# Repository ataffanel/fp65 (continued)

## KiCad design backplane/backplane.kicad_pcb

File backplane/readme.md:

# 4 Board FP65 backplane

Backplane that can accept 4 FP65 boards and that can be chained to other backplane to accomodate bigger system.

A power supply can optionaly be soldered in order to provide up to 5V 1A to the system.
One of the board can also provide power for the system.

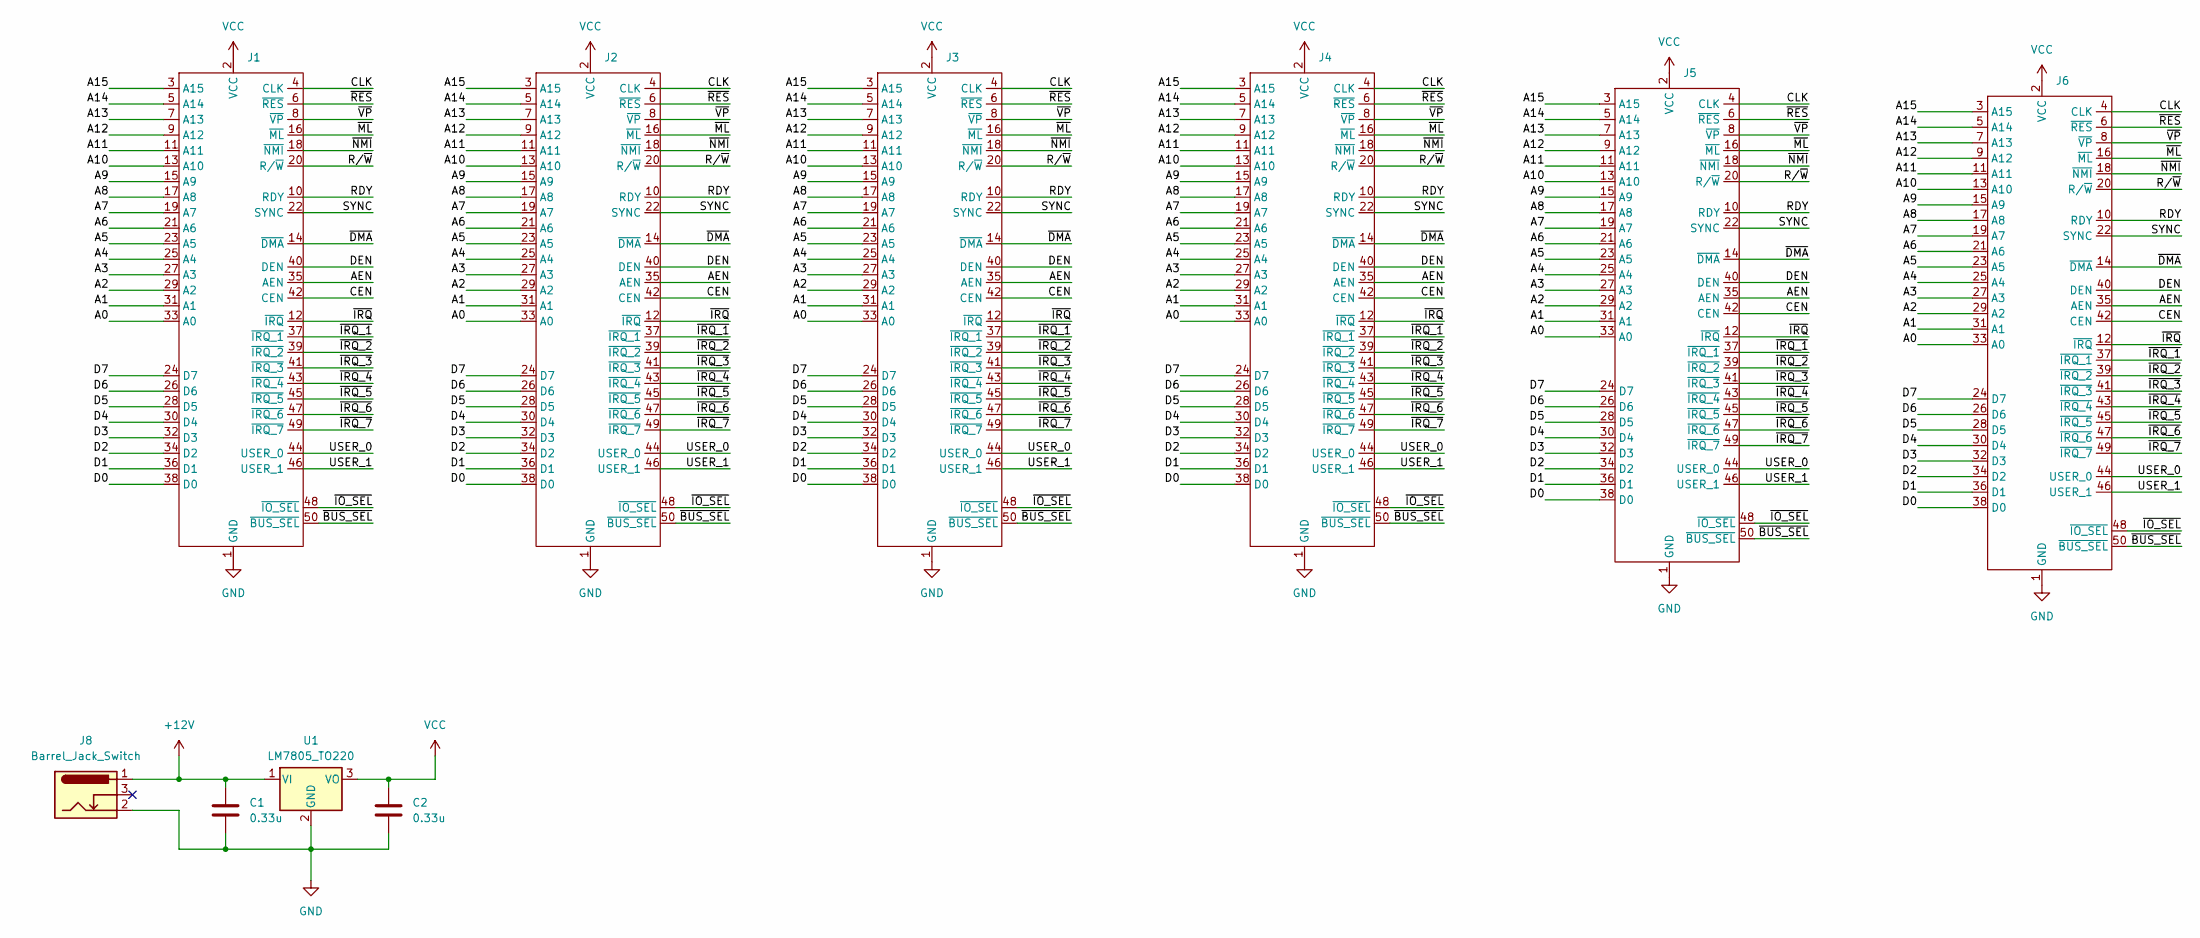
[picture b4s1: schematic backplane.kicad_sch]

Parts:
C1, C2: 0.33u; C_Disc_D5.0mm_W2.5mm_P5.00mm
J1: PinSocket_2x25_P2.54mm_Horizontal
J2, J3, J4, J5: PinSocket_2x25_P2.54mm_Vertical
J6: PinHeader_2x25_P2.54mm_Horizontal
J8: Barrel_Jack_Switch; BarrelJack_GCT_DCJ200-10-A_Horizontal
U1: LM7805_TO220; TO-220-3_Vertical

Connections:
+12V: C1.1, J8.1, U1.1 (VI)
/A0: J1.33 (A0), J2.33 (A0), J3.33 (A0), J4.33 (A0), J5.33 (A0), J6.33 (A0)
/A1: J1.31 (A1), J2.31 (A1), J3.31 (A1), J4.31 (A1), J5.31 (A1), J6.31 (A1)
/A2: J1.29 (A2), J2.29 (A2), J3.29 (A2), J4.29 (A2), J5.29 (A2), J6.29 (A2)
/A3: J1.27 (A3), J2.27 (A3), J3.27 (A3), J4.27 (A3), J5.27 (A3), J6.27 (A3)
/A4: J1.25 (A4), J2.25 (A4), J3.25 (A4), J4.25 (A4), J5.25 (A4), J6.25 (A4)
/A5: J1.23 (A5), J2.23 (A5), J3.23 (A5), J4.23 (A5), J5.23 (A5), J6.23 (A5)
/A6: J1.21 (A6), J2.21 (A6), J3.21 (A6), J4.21 (A6), J5.21 (A6), J6.21 (A6)
/A7: J1.19 (A7), J2.19 (A7), J3.19 (A7), J4.19 (A7), J5.19 (A7), J6.19 (A7)
/A8: J1.17 (A8), J2.17 (A8), J3.17 (A8), J4.17 (A8), J5.17 (A8), J6.17 (A8)
/A9: J1.15 (A9), J2.15 (A9), J3.15 (A9), J4.15 (A9), J5.15 (A9), J6.15 (A9)
/A10: J1.13 (A10), J2.13 (A10), J3.13 (A10), J4.13 (A10), J5.13 (A10), J6.13 (A10)
/A11: J1.11 (A11), J2.11 (A11), J3.11 (A11), J4.11 (A11), J5.11 (A11), J6.11 (A11)
/A12: J1.9 (A12), J2.9 (A12), J3.9 (A12), J4.9 (A12), J5.9 (A12), J6.9 (A12)
/A13: J1.7 (A13), J2.7 (A13), J3.7 (A13), J4.7 (A13), J5.7 (A13), J6.7 (A13)
/A14: J1.5 (A14), J2.5 (A14), J3.5 (A14), J4.5 (A14), J5.5 (A14), J6.5 (A14)
/A15: J1.3 (A15), J2.3 (A15), J3.3 (A15), J4.3 (A15), J5.3 (A15), J6.3 (A15)
/AEN: J1.35 (AEN), J2.35 (AEN), J3.35 (AEN), J4.35 (AEN), J5.35 (AEN), J6.35 (AEN)
/CEN: J1.42 (CEN), J2.42 (CEN), J3.42 (CEN), J4.42 (CEN), J5.42 (CEN), J6.42 (CEN)
/CLK: J1.4 (CLK), J2.4 (CLK), J3.4 (CLK), J4.4 (CLK), J5.4 (CLK), J6.4 (CLK)
/D0: J1.38 (D0), J2.38 (D0), J3.38 (D0), J4.38 (D0), J5.38 (D0), J6.38 (D0)
/D1: J1.36 (D1), J2.36 (D1), J3.36 (D1), J4.36 (D1), J5.36 (D1), J6.36 (D1)
/D2: J1.34 (D2), J2.34 (D2), J3.34 (D2), J4.34 (D2), J5.34 (D2), J6.34 (D2)
/D3: J1.32 (D3), J2.32 (D3), J3.32 (D3), J4.32 (D3), J5.32 (D3), J6.32 (D3)
/D4: J1.30 (D4), J2.30 (D4), J3.30 (D4), J4.30 (D4), J5.30 (D4), J6.30 (D4)
/D5: J1.28 (D5), J2.28 (D5), J3.28 (D5), J4.28 (D5), J5.28 (D5), J6.28 (D5)
/D6: J1.26 (D6), J2.26 (D6), J3.26 (D6), J4.26 (D6), J5.26 (D6), J6.26 (D6)
/D7: J1.24 (D7), J2.24 (D7), J3.24 (D7), J4.24 (D7), J5.24 (D7), J6.24 (D7)
/DEN: J1.40 (DEN), J2.40 (DEN), J3.40 (DEN), J4.40 (DEN), J5.40 (DEN), J6.40 (DEN)
/RDY: J1.10 (RDY), J2.10 (RDY), J3.10 (RDY), J4.10 (RDY), J5.10 (RDY), J6.10 (RDY)
/R/~W: J1.20 (R/~W), J2.20 (R/~W), J3.20 (R/~W), J4.20 (R/~W), J5.20 (R/~W), J6.20 (R/~W)
/SYNC: J1.22 (SYNC), J2.22 (SYNC), J3.22 (SYNC), J4.22 (SYNC), J5.22 (SYNC), J6.22 (SYNC)
/USER_0: J1.44 (USER_0), J2.44 (USER_0), J3.44 (USER_0), J4.44 (USER_0), J5.44 (USER_0), J6.44 (USER_0)
/USER_1: J1.46 (USER_1), J2.46 (USER_1), J3.46 (USER_1), J4.46 (USER_1), J5.46 (USER_1), J6.46 (USER_1)
/~BUS_SEL: J1.50 (~BUS_SEL), J2.50 (~BUS_SEL), J3.50 (~BUS_SEL), J4.50 (~BUS_SEL), J5.50 (~BUS_SEL), J6.50 (~BUS_SEL)
/~DMA: J1.14 (~DMA), J2.14 (~DMA), J3.14 (~DMA), J4.14 (~DMA), J5.14 (~DMA), J6.14 (~DMA)
/~IO_SEL: J1.48 (~IO_SEL), J2.48 (~IO_SEL), J3.48 (~IO_SEL), J4.48 (~IO_SEL), J5.48 (~IO_SEL), J6.48 (~IO_SEL)
/~IRQ_1: J1.37 (~IRQ_1), J2.37 (~IRQ_1), J3.37 (~IRQ_1), J4.37 (~IRQ_1), J5.37 (~IRQ_1), J6.37 (~IRQ_1)
/~IRQ_2: J1.39 (~IRQ_2), J2.39 (~IRQ_2), J3.39 (~IRQ_2), J4.39 (~IRQ_2), J5.39 (~IRQ_2), J6.39 (~IRQ_2)
/~IRQ_3: J1.41 (~IRQ_3), J2.41 (~IRQ_3), J3.41 (~IRQ_3), J4.41 (~IRQ_3), J5.41 (~IRQ_3), J6.41 (~IRQ_3)
/~IRQ_4: J1.43 (~IRQ_4), J2.43 (~IRQ_4), J3.43 (~IRQ_4), J4.43 (~IRQ_4), J5.43 (~IRQ_4), J6.43 (~IRQ_4)
/~IRQ_5: J1.45 (~IRQ_5), J2.45 (~IRQ_5), J3.45 (~IRQ_5), J4.45 (~IRQ_5), J5.45 (~IRQ_5), J6.45 (~IRQ_5)
/~IRQ_6: J1.47 (~IRQ_6), J2.47 (~IRQ_6), J3.47 (~IRQ_6), J4.47 (~IRQ_6), J5.47 (~IRQ_6), J6.47 (~IRQ_6)
/~IRQ_7: J1.49 (~IRQ_7), J2.49 (~IRQ_7), J3.49 (~IRQ_7), J4.49 (~IRQ_7), J5.49 (~IRQ_7), J6.49 (~IRQ_7)
/~IRQ: J1.12 (~IRQ), J2.12 (~IRQ), J3.12 (~IRQ), J4.12 (~IRQ), J5.12 (~IRQ), J6.12 (~IRQ)
/~ML: J1.16 (~ML), J2.16 (~ML), J3.16 (~ML), J4.16 (~ML), J5.16 (~ML), J6.16 (~ML)
/~NMI: J1.18 (~NMI), J2.18 (~NMI), J3.18 (~NMI), J4.18 (~NMI), J5.18 (~NMI), J6.18 (~NMI)
/~RES: J1.6 (~RES), J2.6 (~RES), J3.6 (~RES), J4.6 (~RES), J5.6 (~RES), J6.6 (~RES)
/~VP: J1.8 (~VP), J2.8 (~VP), J3.8 (~VP), J4.8 (~VP), J5.8 (~VP), J6.8 (~VP)
GND: C1.2, C2.2, J1.1 (GND), J2.1 (GND), J3.1 (GND), J4.1 (GND), J5.1 (GND), J6.1 (GND), J8.2, U1.2 (GND)
VCC: C2.1, J1.2 (VCC), J2.2 (VCC), J3.2 (VCC), J4.2 (VCC), J5.2 (VCC), J6.2 (VCC), U1.3 (VO)

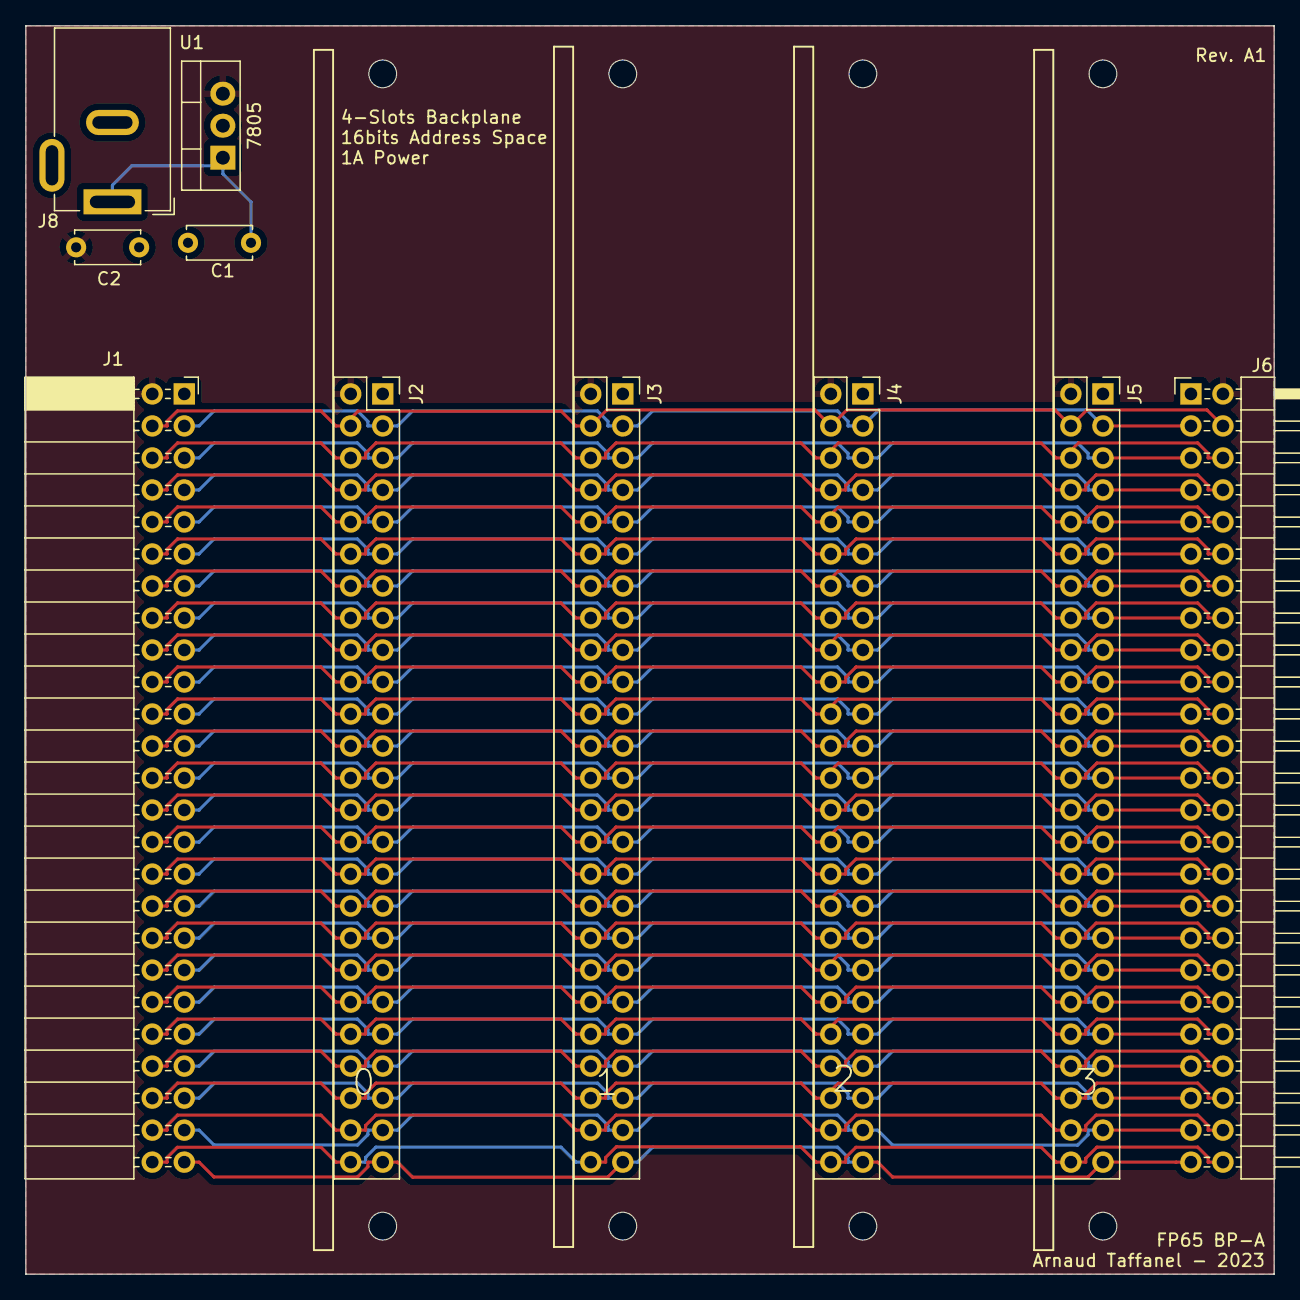
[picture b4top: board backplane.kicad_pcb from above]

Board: 2 copper layers, 99.1 x 99.1 mm, 10 parts (0 on the bottom side), 51 nets.

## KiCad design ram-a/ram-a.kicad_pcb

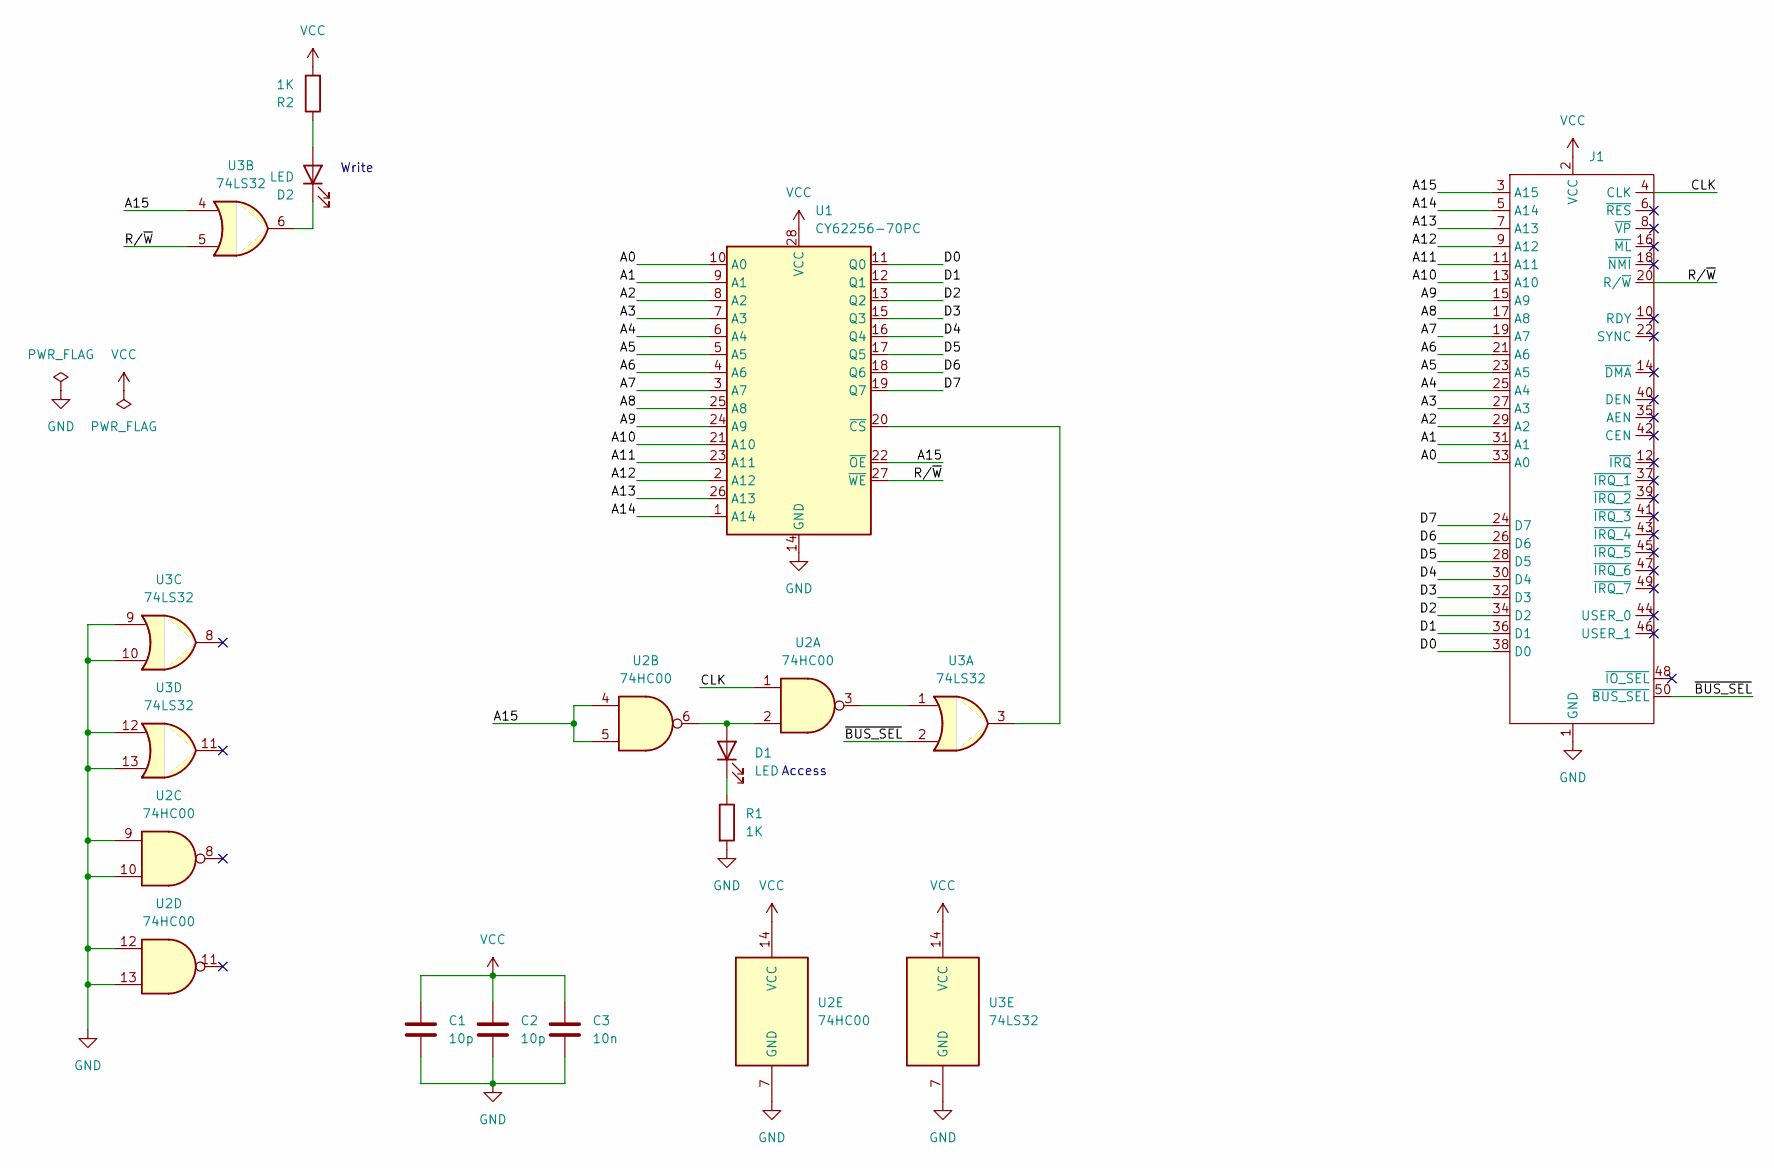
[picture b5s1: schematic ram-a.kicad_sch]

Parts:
C1, C2: 10p; C_Disc_D4.3mm_W1.9mm_P5.00mm
C3: 10n; C_Disc_D4.3mm_W1.9mm_P5.00mm
D1, D2: LED; LED_D3.0mm_Horizontal_O1.27mm_Z2.0mm
J1: PinHeader_2x25_P2.54mm_Horizontal
R1, R2: 1K; R_Axial_DIN0204_L3.6mm_D1.6mm_P7.62mm_Horizontal
U1: CY62256-70PC; DIP-28_W15.24mm
U2: 74HC00; DIP-14_W7.62mm
U3: 74LS32; DIP-14_W7.62mm

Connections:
/A0: J1.33 (A0), U1.10 (A0)
/A1: J1.31 (A1), U1.9 (A1)
/A2: J1.29 (A2), U1.8 (A2)
/A3: J1.27 (A3), U1.7 (A3)
/A4: J1.25 (A4), U1.6 (A4)
/A5: J1.23 (A5), U1.5 (A5)
/A6: J1.21 (A6), U1.4 (A6)
/A7: J1.19 (A7), U1.3 (A7)
/A8: J1.17 (A8), U1.25 (A8)
/A9: J1.15 (A9), U1.24 (A9)
/A10: J1.13 (A10), U1.21 (A10)
/A11: J1.11 (A11), U1.23 (A11)
/A12: J1.9 (A12), U1.2 (A12)
/A13: J1.7 (A13), U1.26 (A13)
/A14: J1.5 (A14), U1.1 (A14)
/A15: J1.3 (A15), U1.22 (~OE), U2.4, U2.5, U3.4
/CLK: J1.4 (CLK), U2.1
/D0: J1.38 (D0), U1.11 (Q0)
/D1: J1.36 (D1), U1.12 (Q1)
/D2: J1.34 (D2), U1.13 (Q2)
/D3: J1.32 (D3), U1.15 (Q3)
/D4: J1.30 (D4), U1.16 (Q4)
/D5: J1.28 (D5), U1.17 (Q5)
/D6: J1.26 (D6), U1.18 (Q6)
/D7: J1.24 (D7), U1.19 (Q7)
/R/~W: J1.20 (R/~W), U1.27 (~WE), U3.5
/~BUS_SEL: J1.50 (~BUS_SEL), U3.2
GND: C1.2, C2.2, C3.2, J1.1 (GND), R1.2, U1.14 (GND), U2.7 (GND), U2.9, U2.10, U2.12, U2.13, U3.7 (GND), U3.9, U3.10, U3.12, U3.13
unnamed: D1.2 (A), U2.2, U2.6
unnamed: D1.1 (K), R1.1
unnamed: D2.2 (A), R2.1
unnamed: D2.1 (K), U3.6
unnamed: U1.20 (~CS), U3.3
unnamed: U2.3, U3.1
VCC: C1.1, C2.1, C3.1, J1.2 (VCC), R2.2, U1.28 (VCC), U2.14 (VCC), U3.14 (VCC)

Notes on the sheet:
Access
Write

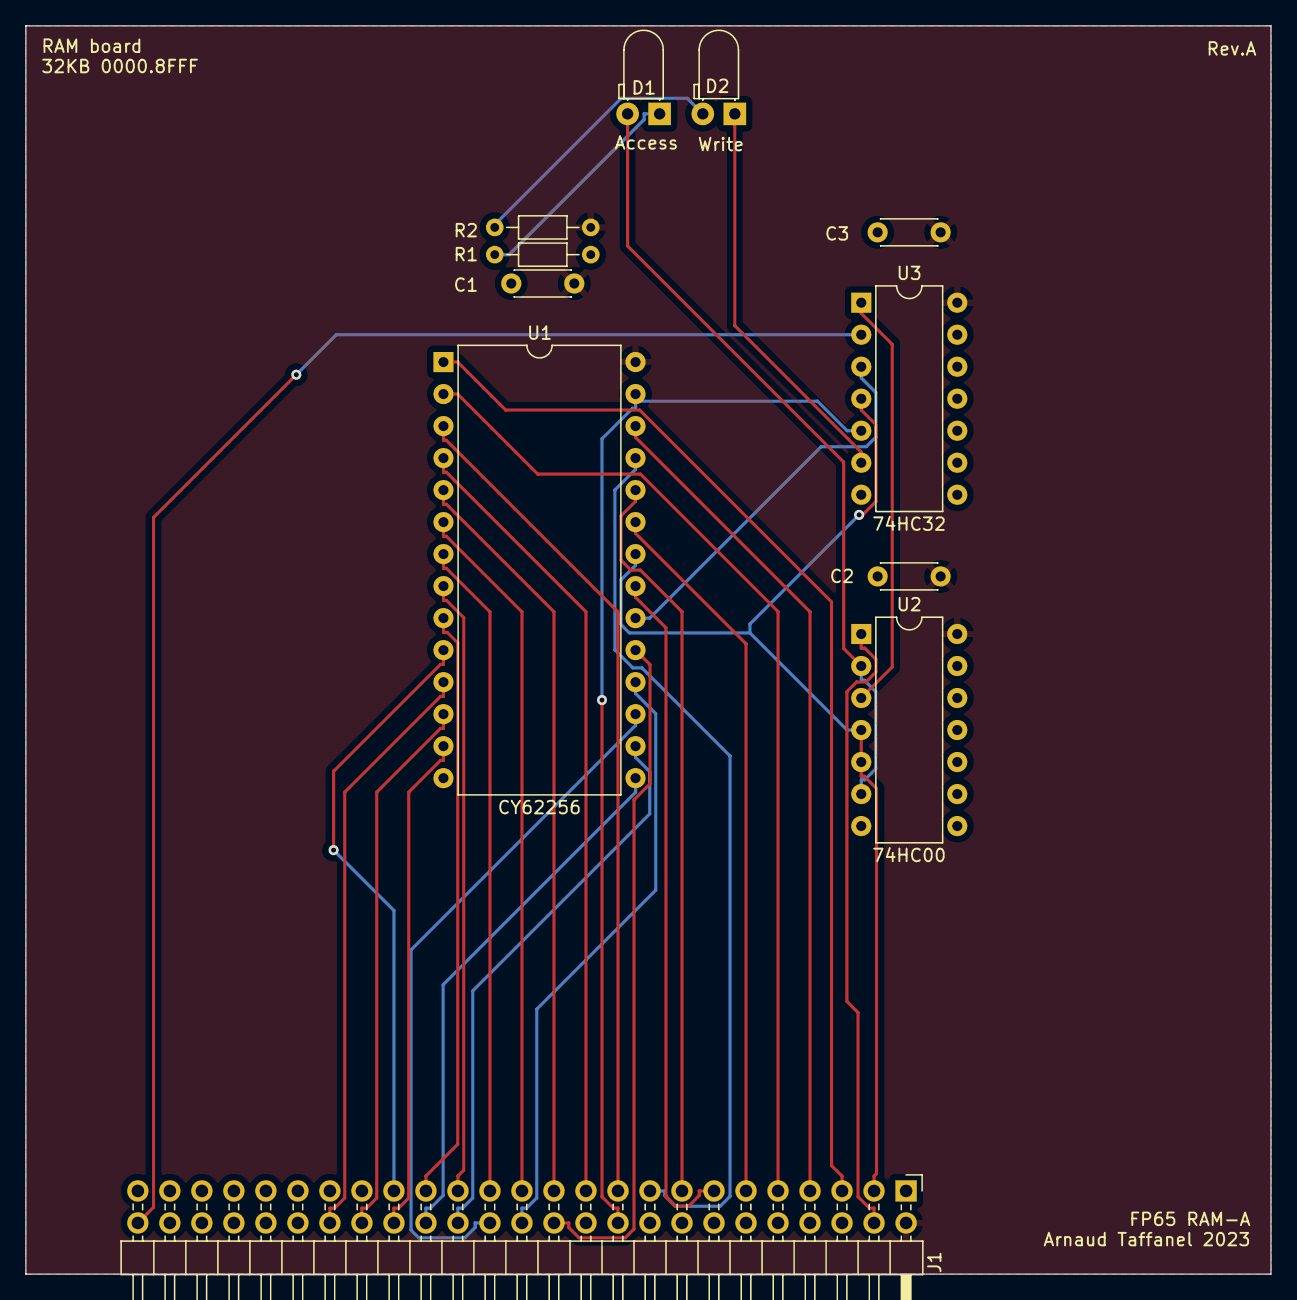
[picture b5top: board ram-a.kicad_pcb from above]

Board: 2 copper layers, 98.8 x 99.1 mm, 11 parts (0 on the bottom side), 35 nets.

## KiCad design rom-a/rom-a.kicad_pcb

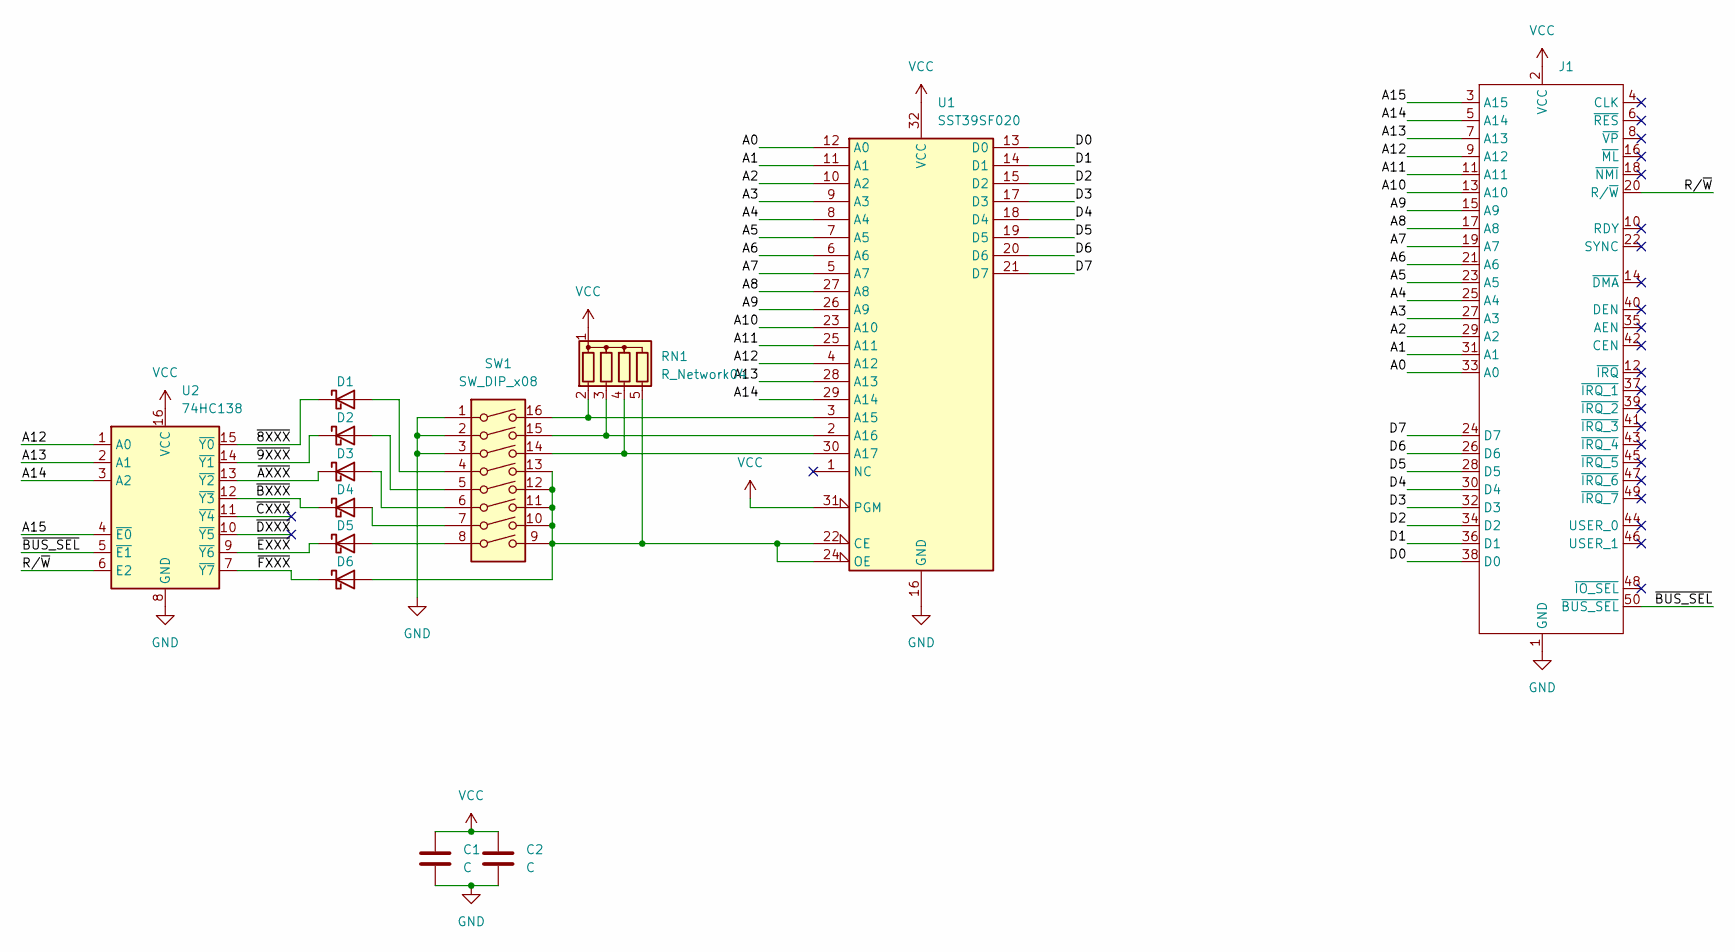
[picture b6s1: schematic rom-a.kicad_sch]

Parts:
C1, C2: C; C_Disc_D3.4mm_W2.1mm_P2.50mm
D1, D2, D3, D4, D5, D6: D_Schottky; D_DO-35_SOD27_P7.62mm_Horizontal
J1: PinHeader_2x25_P2.54mm_Horizontal
RN1: R_Network04; R_Array_SIP5
SW1: SW_DIP_x08; SW_DIP_SPSTx08_Slide_9.78x22.5mm_W7.62mm_P2.54mm
U1: SST39SF020; DIP-32_W15.24mm
U2: 74HC138; DIP-16_W7.62mm

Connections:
/A0: J1.33 (A0), U1.12 (A0)
/A1: J1.31 (A1), U1.11 (A1)
/A2: J1.29 (A2), U1.10 (A2)
/A3: J1.27 (A3), U1.9 (A3)
/A4: J1.25 (A4), U1.8 (A4)
/A5: J1.23 (A5), U1.7 (A5)
/A6: J1.21 (A6), U1.6 (A6)
/A7: J1.19 (A7), U1.5 (A7)
/A8: J1.17 (A8), U1.27 (A8)
/A9: J1.15 (A9), U1.26 (A9)
/A10: J1.13 (A10), U1.23 (A10)
/A11: J1.11 (A11), U1.25 (A11)
/A12: J1.9 (A12), U1.4 (A12), U2.1 (A0)
/A13: J1.7 (A13), U1.28 (A13), U2.2 (A1)
/A14: J1.5 (A14), U1.29 (A14), U2.3 (A2)
/A15: J1.3 (A15), U2.4 (~E0)
/D0: J1.38 (D0), U1.13 (D0)
/D1: J1.36 (D1), U1.14 (D1)
/D2: J1.34 (D2), U1.15 (D2)
/D3: J1.32 (D3), U1.17 (D3)
/D4: J1.30 (D4), U1.18 (D4)
/D5: J1.28 (D5), U1.19 (D5)
/D6: J1.26 (D6), U1.20 (D6)
/D7: J1.24 (D7), U1.21 (D7)
/R/~W: J1.20 (R/~W), U2.6 (E2)
/~8XXX: D1.1 (K), U2.15 (~Y0)
/~9XXX: D2.1 (K), U2.14 (~Y1)
/~AXXX: D3.1 (K), U2.13 (~Y2)
/~BUS_SEL: J1.50 (~BUS_SEL), U2.5 (~E1)
/~BXXX: D4.1 (K), U2.12 (~Y3)
/~CXXX: U2.11 (~Y4)
/~DXXX: U2.10 (~Y5)
/~EXXX: D5.1 (K), U2.9 (~Y6)
/~FXXX: D6.1 (K), U2.7 (~Y7)
GND: C1.2, C2.2, J1.1 (GND), SW1.1, SW1.2, SW1.3, U1.16 (GND), U2.8 (GND)
unnamed: D1.2 (A), SW1.4
unnamed: D2.2 (A), SW1.5
unnamed: D3.2 (A), SW1.6
unnamed: D4.2 (A), SW1.7
unnamed: D5.2 (A), SW1.8
unnamed: D6.2 (A), RN1.5 (R4), SW1.9, SW1.10, SW1.11, SW1.12, SW1.13, U1.22 (CE), U1.24 (OE)
unnamed: RN1.2 (R1), SW1.16, U1.3 (A15)
unnamed: RN1.3 (R2), SW1.15, U1.2 (A16)
unnamed: RN1.4 (R3), SW1.14, U1.30 (A17)
VCC: C1.1, C2.1, J1.2 (VCC), RN1.1 (common), U1.31 (PGM), U1.32 (VCC), U2.16 (VCC)

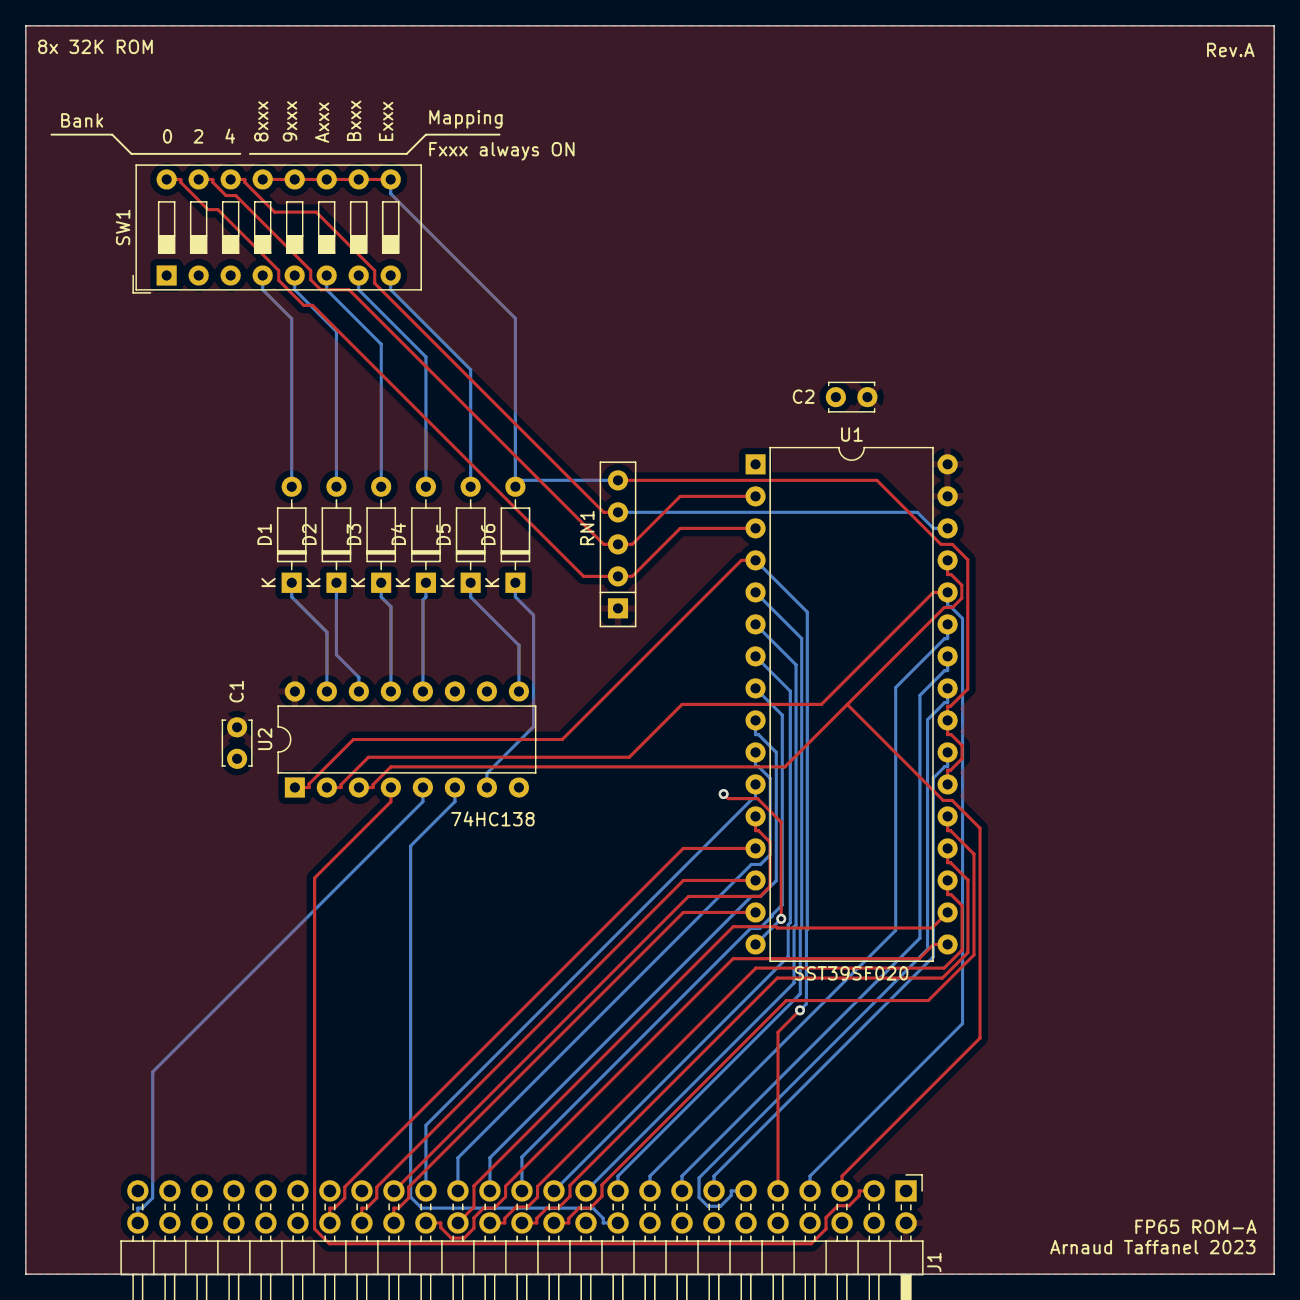
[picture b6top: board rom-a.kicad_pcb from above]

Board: 2 copper layers, 99.1 x 99.1 mm, 13 parts (0 on the bottom side), 43 nets.

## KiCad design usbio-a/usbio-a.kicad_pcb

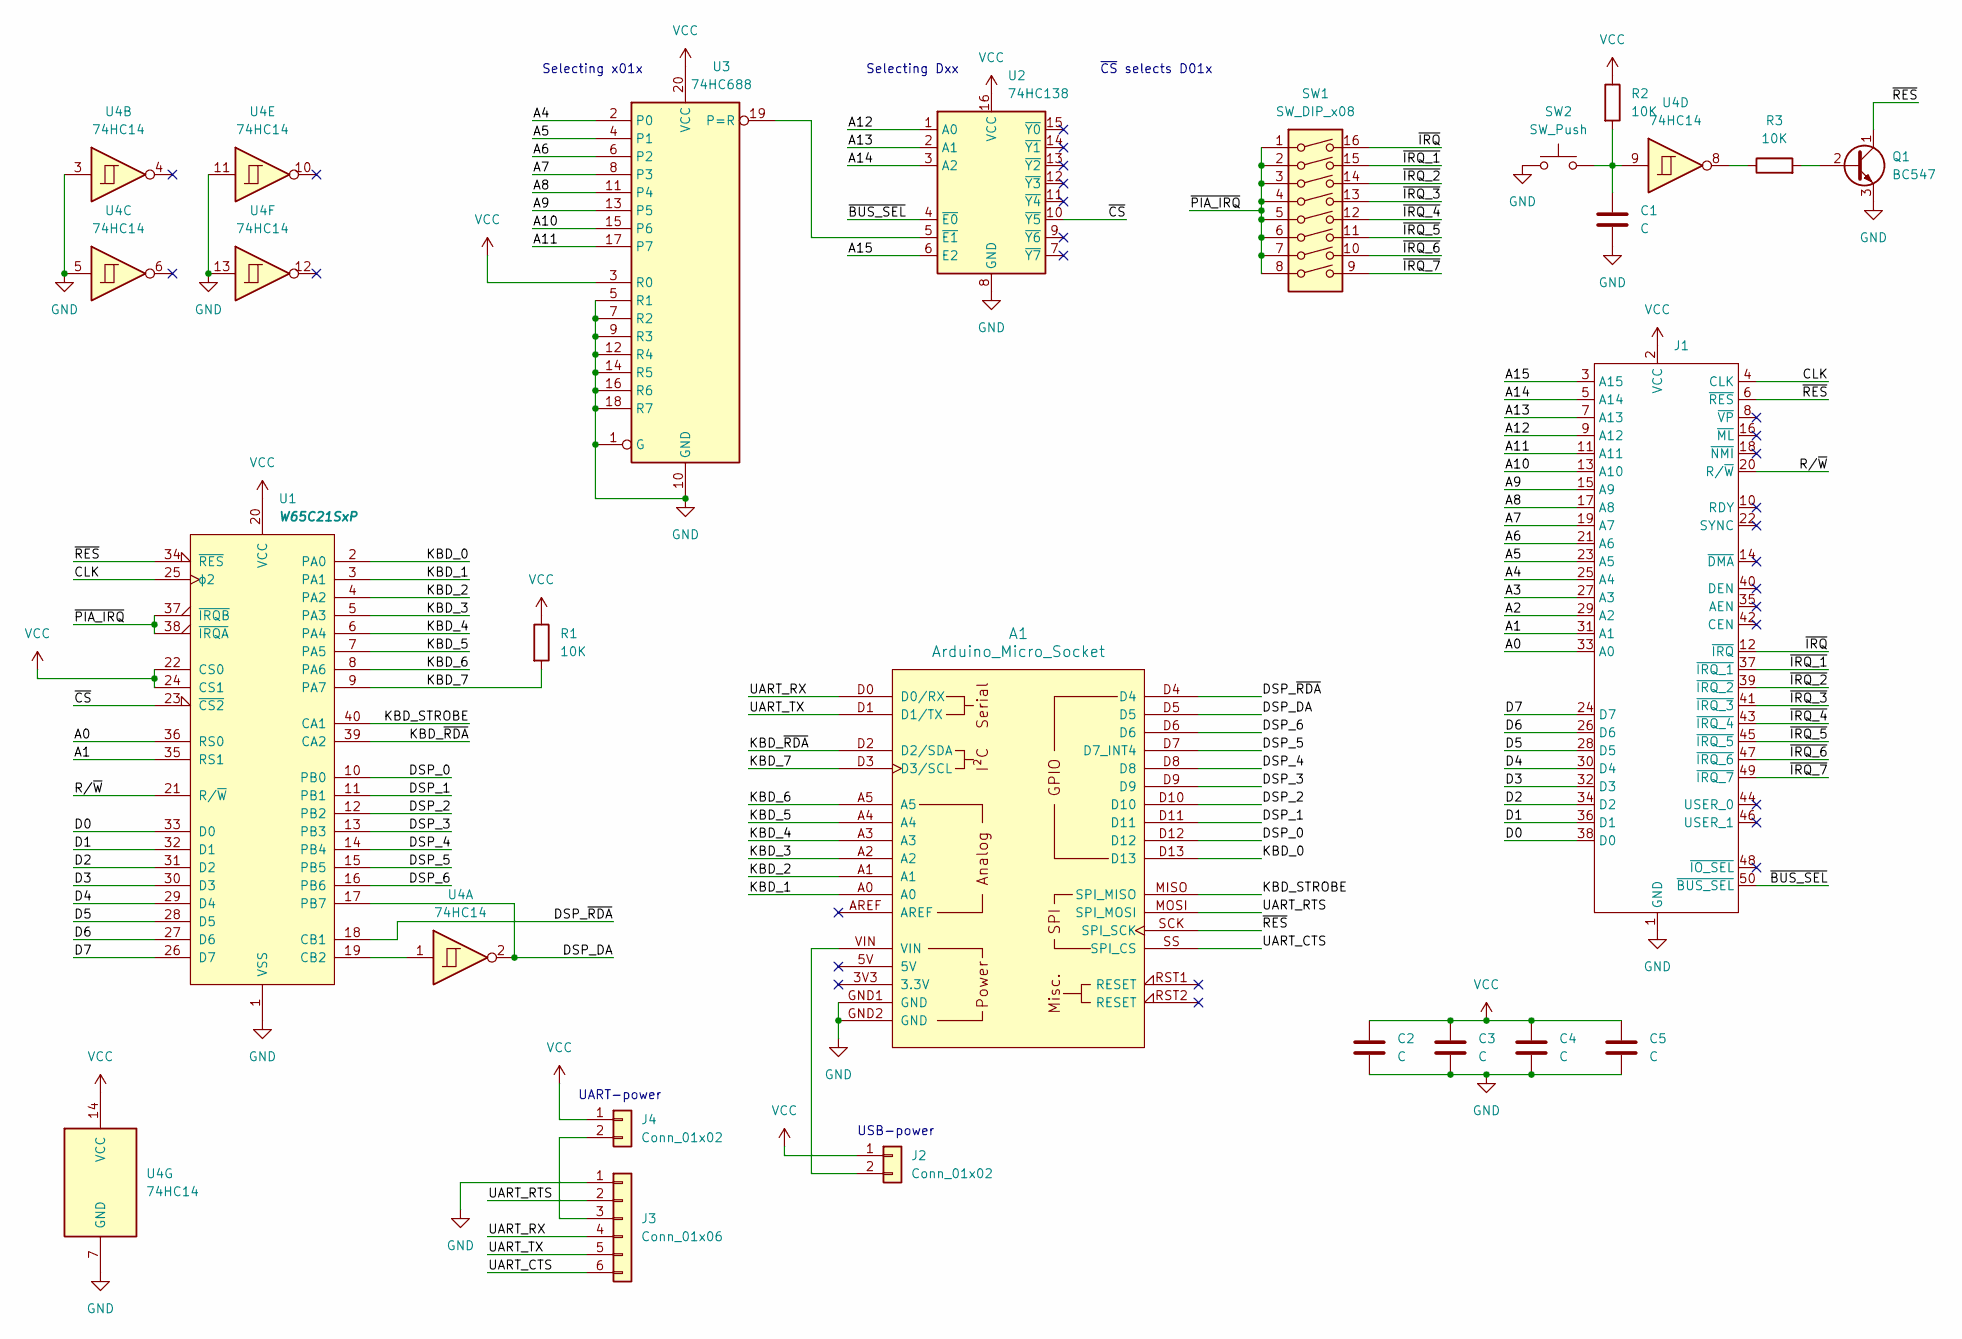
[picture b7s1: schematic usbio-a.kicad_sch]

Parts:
A1: Arduino_Micro_Socket
C1, C2, C3, C4, C5: C; C_Disc_D4.7mm_W2.5mm_P5.00mm
J1: PinHeader_2x25_P2.54mm_Horizontal
J2, J4: Conn_01x02; PinHeader_1x02_P2.54mm_Vertical
J3: Conn_01x06; PinHeader_1x06_P2.54mm_Horizontal
Q1: BC547; TO-92_Inline
R1, R2, R3: 10K; R_Axial_DIN0207_L6.3mm_D2.5mm_P15.24mm_Horizontal
SW1: SW_DIP_x08; SW_DIP_SPSTx08_Slide_9.78x22.5mm_W7.62mm_P2.54mm
SW2: SW_Push; SW_PUSH_6mm
U1: W65C21SxP; DIP-40_W15.24mm
U2: 74HC138; DIP-16_W7.62mm
U3: 74HC688; DIP-20_W7.62mm
U4: 74HC14; DIP-14_W7.62mm

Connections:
/A0: J1.33 (A0), U1.36 (RS0)
/A1: J1.31 (A1), U1.35 (RS1)
/A2: J1.29 (A2)
/A3: J1.27 (A3)
/A4: J1.25 (A4), U3.2 (P0)
/A5: J1.23 (A5), U3.4 (P1)
/A6: J1.21 (A6), U3.6 (P2)
/A7: J1.19 (A7), U3.8 (P3)
/A8: J1.17 (A8), U3.11 (P4)
/A9: J1.15 (A9), U3.13 (P5)
/A10: J1.13 (A10), U3.15 (P6)
/A11: J1.11 (A11), U3.17 (P7)
/A12: J1.9 (A12), U2.1 (A0)
/A13: J1.7 (A13), U2.2 (A1)
/A14: J1.5 (A14), U2.3 (A2)
/A15: J1.3 (A15), U2.6 (E2)
/CLK: J1.4 (CLK), U1.25 (ϕ2)
/D0: J1.38 (D0), U1.33 (D0)
/D1: J1.36 (D1), U1.32 (D1)
/D2: J1.34 (D2), U1.31 (D2)
/D3: J1.32 (D3), U1.30 (D3)
/D4: J1.30 (D4), U1.29 (D4)
/D5: J1.28 (D5), U1.28 (D5)
/D6: J1.26 (D6), U1.27 (D6)
/D7: J1.24 (D7), U1.26 (D7)
/DSP_0: A1.D12, U1.10 (PB0)
/DSP_1: A1.D11, U1.11 (PB1)
/DSP_2: A1.D10, U1.12 (PB2)
/DSP_3: A1.D9, U1.13 (PB3)
/DSP_4: A1.D8, U1.14 (PB4)
/DSP_5: A1.D7 (D7_INT4), U1.15 (PB5)
/DSP_6: A1.D6, U1.16 (PB6)
/DSP_DA: A1.D5, U1.17 (PB7), U4.2
/DSP_~RDA: A1.D4, U1.18 (CB1)
/KBD_0: A1.D13, U1.2 (PA0)
/KBD_1: A1.A0, U1.3 (PA1)
/KBD_2: A1.A1, U1.4 (PA2)
/KBD_3: A1.A2, U1.5 (PA3)
/KBD_4: A1.A3, U1.6 (PA4)
/KBD_5: A1.A4, U1.7 (PA5)
/KBD_6: A1.A5, U1.8 (PA6)
/KBD_7: A1.D3 (D3/SCL), R1.2, U1.9 (PA7)
/KBD_STROBE: A1.MISO (SPI_MISO), U1.40 (CA1)
/KBD_~RDA: A1.D2 (D2/SDA), U1.39 (CA2)
/R/~W: J1.20 (R/~W), U1.21 (R/~W)
/UART_CTS: A1.SS (SPI_CS), J3.6
/UART_RTS: A1.MOSI (SPI_MOSI), J3.2
/UART_RX: A1.D0 (D0/RX), J3.4
/UART_TX: A1.D1 (D1/TX), J3.5
/~BUS_SEL: J1.50 (~BUS_SEL), U2.4 (~E0)
/~CS: U1.23 (~CS2), U2.10 (~Y5)
/~IRQ_1: J1.37 (~IRQ_1), SW1.15
/~IRQ_2: J1.39 (~IRQ_2), SW1.14
/~IRQ_3: J1.41 (~IRQ_3), SW1.13
/~IRQ_4: J1.43 (~IRQ_4), SW1.12
/~IRQ_5: J1.45 (~IRQ_5), SW1.11
/~IRQ_6: J1.47 (~IRQ_6), SW1.10
/~IRQ_7: J1.49 (~IRQ_7), SW1.9
/~IRQ: J1.12 (~IRQ), SW1.16
/~PIA_IRQ: SW1.1, SW1.2, SW1.3, SW1.4, SW1.5, SW1.6, SW1.7, SW1.8, U1.37 (~IRQB), U1.38 (~IRQA)
/~RES: A1.SCK (SPI_SCK), J1.6 (~RES), Q1.1 (C), U1.34 (~RES)
GND: A1.GND1 (GND), A1.GND2 (GND), C1.2, C2.2, C3.2, C4.2, C5.2, J1.1 (GND), J3.1, Q1.3 (E), SW2.1, U1.1 (VSS), U2.8 (GND), U3.1 (G), U3.5 (R1), U3.7 (R2), U3.9 (R3), U3.10 (GND), U3.12 (R4), U3.14 (R5), U3.16 (R6), U3.18 (R7), U4.3, U4.5, U4.7 (GND), U4.11, U4.13
unnamed: C1.1, R2.2, SW2.2, U4.9
unnamed: A1.VIN, J2.2
unnamed: J3.3, J4.2
unnamed: Q1.2 (B), R3.2
unnamed: R3.1, U4.8
unnamed: U1.19 (CB2), U4.1
unnamed: U2.5 (~E1), U3.19 (P=R)
VCC: C2.1, C3.1, C4.1, C5.1, J1.2 (VCC), J2.1, J4.1, R1.1, R2.1, U1.20 (VCC), U1.22 (CS0), U1.24 (CS1), U2.16 (VCC), U3.3 (R0), U3.20 (VCC), U4.14 (VCC)

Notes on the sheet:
UART-power
~{CS} selects D01x
Selecting Dxx
Selecting x01x
USB-power

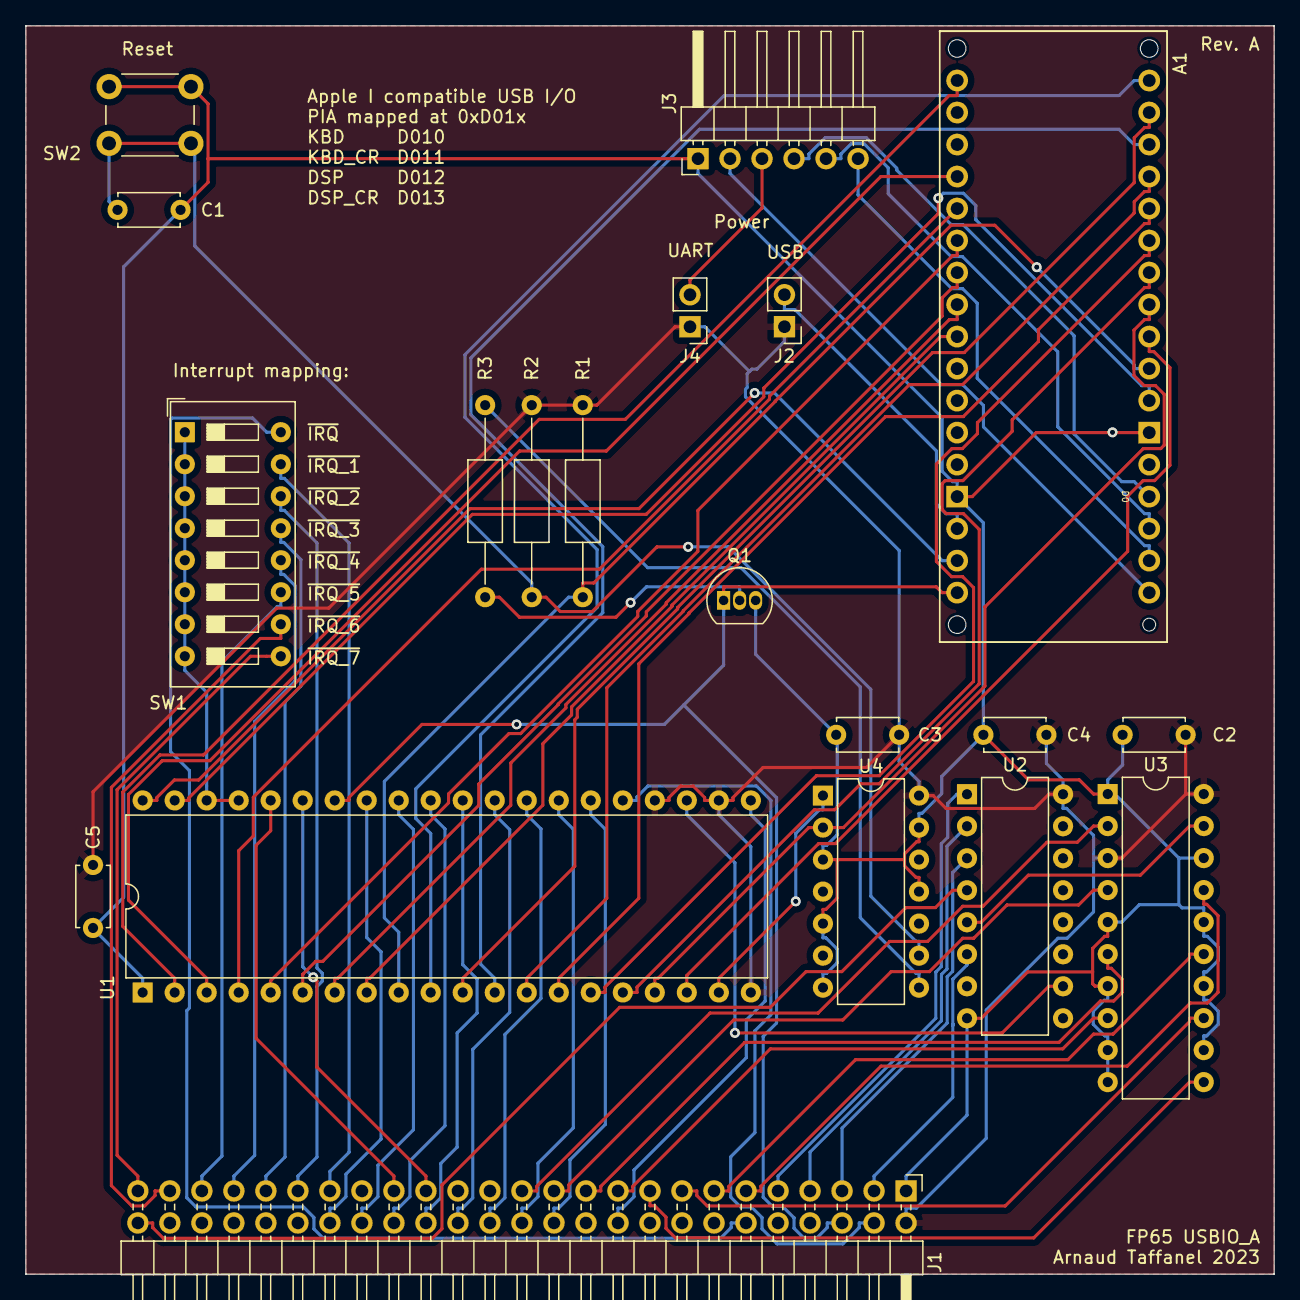
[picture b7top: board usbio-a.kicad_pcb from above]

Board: 2 copper layers, 99.1 x 99.1 mm, 20 parts (0 on the bottom side), 68 nets.

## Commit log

2023-10-23 Initial ordered board
2023-12-28 Add mounting/alignement holes to backplane
2023-12-28 Specify resistors values to MPU-A
2023-12-28 Add SCSI-A board: 8 bits SCSI SC interface
2023-12-28 Add SIO-A board: RS232 Serial I/0 and VIA PIO/Timer
2023-12-28 Minimal change to fix SCSI CPU-Bus connection
2023-12-28 Fix SIO-A CPU bus R/W logic
2023-12-28 Fix DB footprint on SCSI-A and SIO-A
2024-03-17 Add license information
2024-03-25 Add some more description and some photos
2024-03-25 Fix typo in Readme
